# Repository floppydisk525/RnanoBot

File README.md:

# RnanoBot
This github repository contains the KiCAD files and supporting documents for an Arduino Nano shield containing a TB6612 motor driver chip and LSM9DS1TR 9DOF IMU.  

The TB6612 circuit was influenced from https://github.com/floppydisk525/BoxBotCtrlBrd, which in turn was influenced from https://github.com/BoxBots/control-board.  

The LSM9DS1TR chip was influenced from sparkfun projects such as https://www.sparkfun.com/products/13944 and others.  

The repository name RnanoBot comes from "aRduino NANO roBOT" motor shield with TB6612 &amp; LSM9DS1TR.  

### Datasheets  
Datasheets are in the https://github.com/floppydisk525/RnanoBot/tree/master/board/datasheets folder.  
# Typical Application Notes  
Here are typical application images for key componets.  
## TB6612  
![alt text][tb6612]  
## LSM9DS1TR  
![alt text][lsm9ds1]  
The following cut/paste is from:  https://learn.sparkfun.com/tutorials/lsm9ds1-breakout-hookup-guide:  
![alt text][lsm9ds1_spark]  

## Arduino NANO Pinout  
I really like this Arduino NANO pinout from Components 101 https://components101.com/microcontrollers/arduino-nano:  
![alt text][ardnano]

![alt text][ard_dim]

### References
https://learn.sparkfun.com/tutorials/lsm9ds1-breakout-hookup-guide  
https://www.sparkfun.com/products/13944  
https://cdn.sparkfun.com/assets/b/0/f/7/4/SparkFun_Motor_Driver-TB6612FNG_v11c.pdf  
https://www.digikey.com/product-detail/en/stmicroelectronics/LSM9DS1TR/497-14946-1-ND/4988079  
https://www.digikey.com/product-detail/en/toshiba-semiconductor-and-storage/TB6612FNGC8EL/TB6612FNGC8ELCT-ND/1730134  
https://components101.com/microcontrollers/arduino-nano  
https://www.youtube.com/watch?v=gGix1oYhTRs  
https://www.st.com/resource/en/datasheet/lsm9ds1.pdf  
http://cheasokchenda.blogspot.com/2018/05/you-can-click-on-link-bellow-to-get-6.html  

[tb6612]:/board/datasheets/tb6612%20typical%20application%20diagram.PNG "TB6612 Typical Application Diagram"
[lsm9ds1]:/board/datasheets/lsm9ds1%20application%20hints.PNG "LSM9DS1TR Application Hint from Datasheet"
[lsm9ds1_spark]:/board/datasheets/sparkfun%20i2c%20wiring%20image.PNG "LSM9DS1TR Spark Fun I2C Wiring example"
[ardnano]:/board/datasheets/Arduino-Nano-Pinout.png "Arduino NANO Pinout from Components 101"
[ard_dim]:/board/datasheets/arduino%20nano%20dim.PNG "Arduino Physical Dimensions"

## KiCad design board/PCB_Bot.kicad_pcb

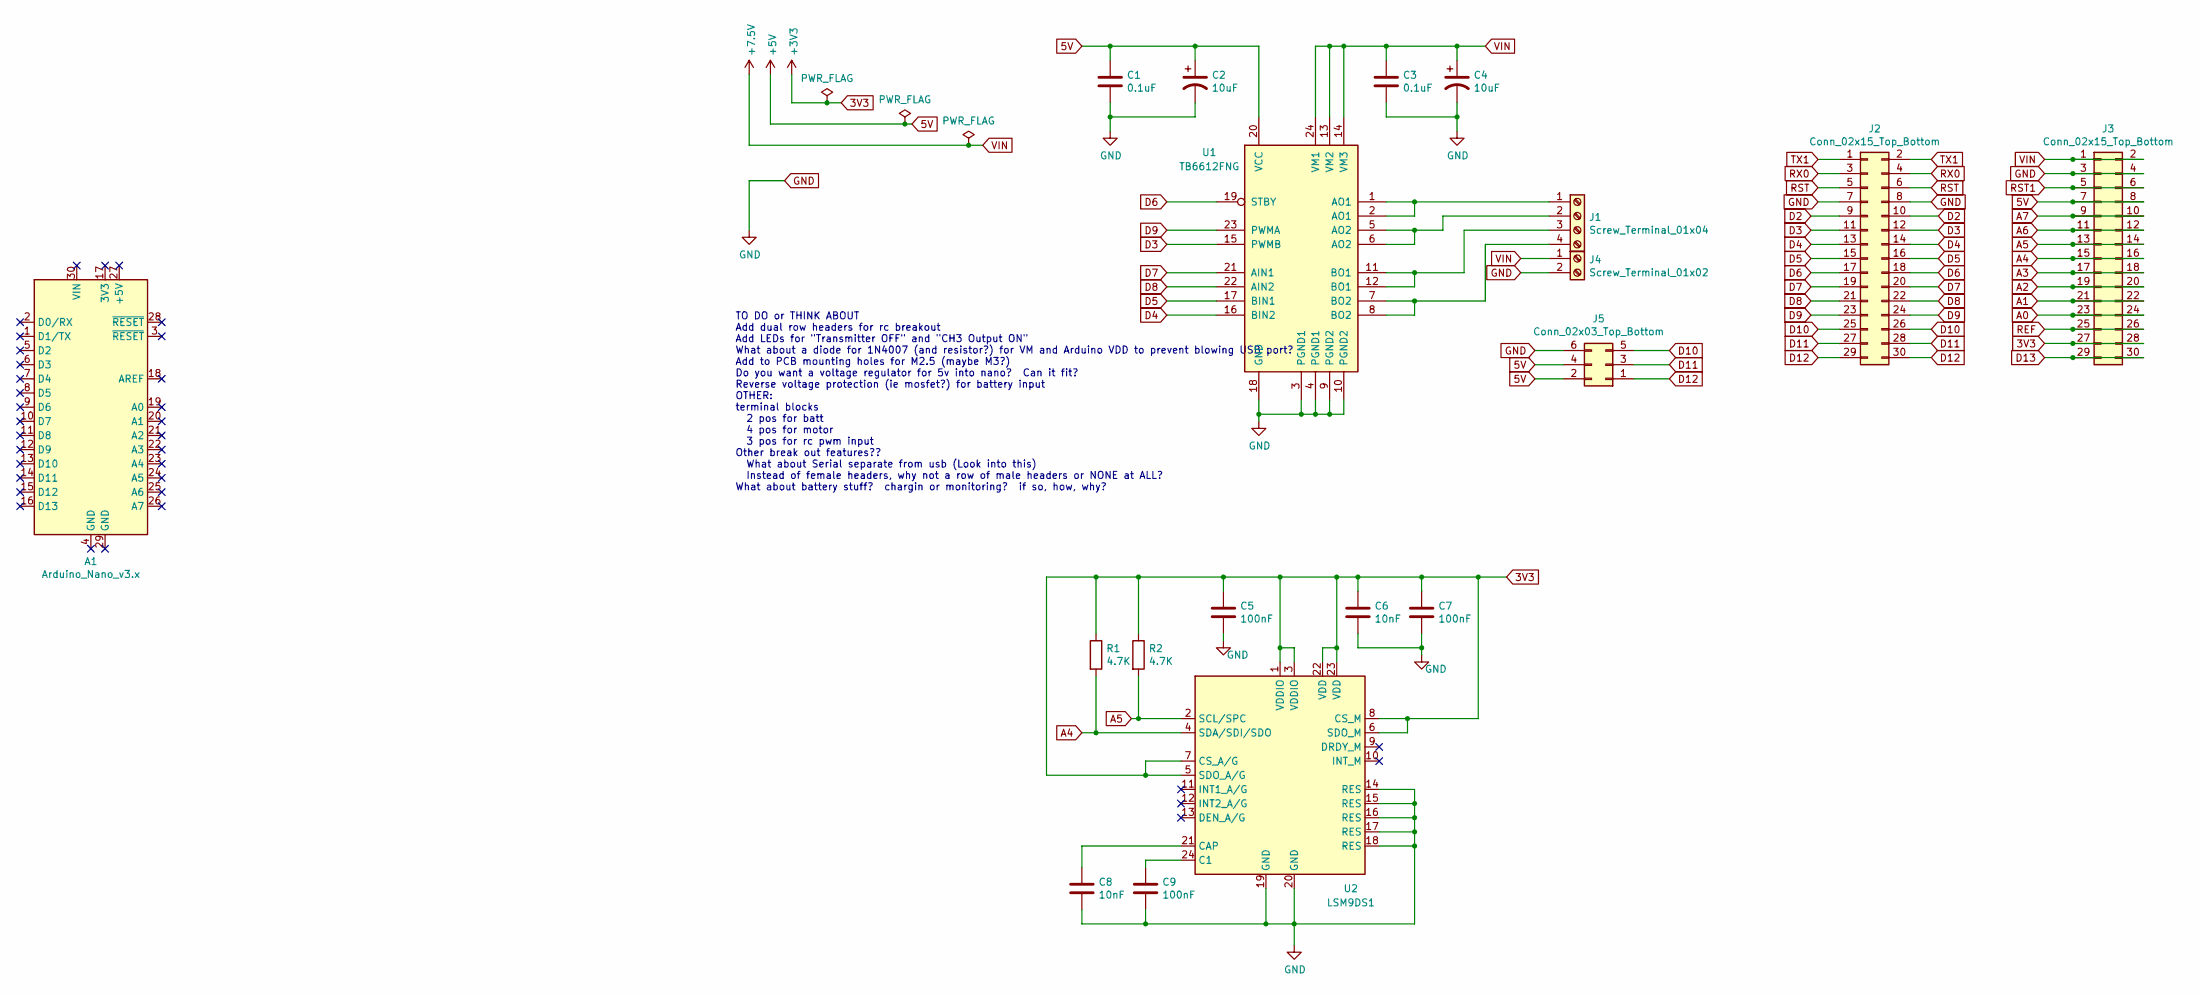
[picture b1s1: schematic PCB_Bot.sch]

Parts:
A1: Arduino_Nano_v3.x; Arduino_Nano
C1, C3: 0.1uF; C_01005_0402Metric
C2, C4: 10uF; C_0201_0603Metric
C5, C7, C9: 100nF; C_01005_0402Metric
C6, C8: 10nF; C_0201_0603Metric
J1: Screw_Terminal_01x04; PTSM_Phoenix_Contact_4-pos_Base_Strip_1815280
J2, J3: Conn_02x15_Top_Bottom; PinSocket_2x15_P2.54mm_Vertical
J4: Screw_Terminal_01x02; PTSM_Phoenix_Contact_2-pos_Base_Strip_1815264
J5: Conn_02x03_Top_Bottom; PinHeader_2x03_P2.54mm_Horizontal
R1, R2: 4.7K; R_01005_0402Metric
U1: TB6612FNG; SSOP-24_5.3x8.2mm_P0.65mm
U2: LSM9DS1; LGA-24L_3x3.5mm_P0.43mm

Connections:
3V3: C5.1, C6.1, C7.1, J3.27, J3.28, R1.1, R2.1, U2.1 (VDDIO), U2.3 (VDDIO), U2.5 (SDO_A/G), U2.6 (SDO_M), U2.7 (CS_A/G), U2.8 (CS_M), U2.22 (VDD), U2.23 (VDD)
5V: C1.1, C2.1, J3.7, J3.8, J5.2, J5.4, U1.20 (VCC)
A0: J3.23, J3.24
A1: J3.21, J3.22
A2: J3.19, J3.20
A3: J3.17, J3.18
A4: J3.15, J3.16, R1.2, U2.4 (SDA/SDI/SDO)
A5: J3.13, J3.14, R2.2, U2.2 (SCL/SPC)
A6: J3.11, J3.12
A7: J3.9, J3.10
D2: J2.9, J2.10
D3: J2.11, J2.12, U1.15 (PWMB)
D4: J2.13, J2.14, U1.16 (BIN2)
D5: J2.15, J2.16, U1.17 (BIN1)
D6: J2.17, J2.18, U1.19 (STBY)
D7: J2.19, J2.20, U1.21 (AIN1)
D8: J2.21, J2.22, U1.22 (AIN2)
D9: J2.23, J2.24, U1.23 (PWMA)
D10: J2.25, J2.26, J5.5
D11: J2.27, J2.28, J5.3
D12: J2.29, J2.30, J5.1
D13: J3.29, J3.30
GND: C1.2, C2.2, C3.2, C4.2, C5.2, C6.2, C7.2, C8.2, C9.2, J2.7, J2.8, J3.3, J3.4, J4.2, J5.6, U1.3 (PGND1), U1.4 (PGND1), U1.9 (PGND2), U1.10 (PGND2), U1.18 (GND), U2.14 (RES), U2.15 (RES), U2.16 (RES), U2.17 (RES), U2.18 (RES), U2.19 (GND), U2.20 (GND)
unnamed: C8.1, U2.21 (CAP)
unnamed: C9.1, U2.24 (C1)
unnamed: J1.1, U1.1 (AO1), U1.2 (AO1)
unnamed: J1.2, U1.5 (AO2), U1.6 (AO2)
unnamed: J1.3, U1.11 (BO1), U1.12 (BO1)
unnamed: J1.4, U1.7 (BO2), U1.8 (BO2)
REF: J3.25, J3.26
RST: J2.5, J2.6
RST1: J3.5, J3.6
RX0: J2.3, J2.4
TX1: J2.1, J2.2
VIN: C3.1, C4.1, J3.1, J3.2, J4.1, U1.13 (VM2), U1.14 (VM3), U1.24 (VM1)

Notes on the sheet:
TO DO or THINK ABOUT Add dual row headers for rc breakout Add LEDs for "Transmitter OFF" and "CH3 Output ON" What about a diode for 1N4007 (and resistor?) for VM and Arduino VDD to prevent blowing USB port? Add to PCB mounting holes for M2.5 (maybe M3?) Do you want a voltage regulator for 5v into n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

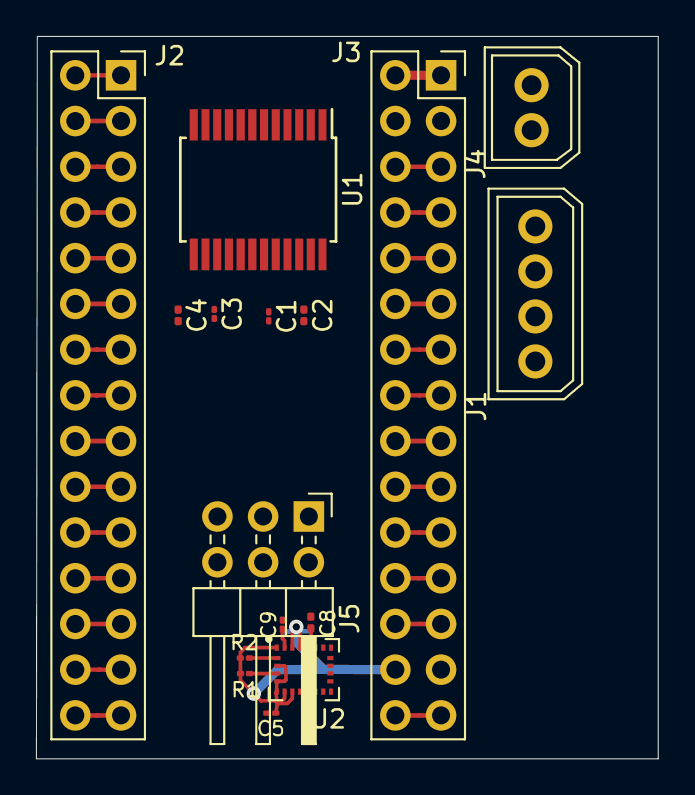
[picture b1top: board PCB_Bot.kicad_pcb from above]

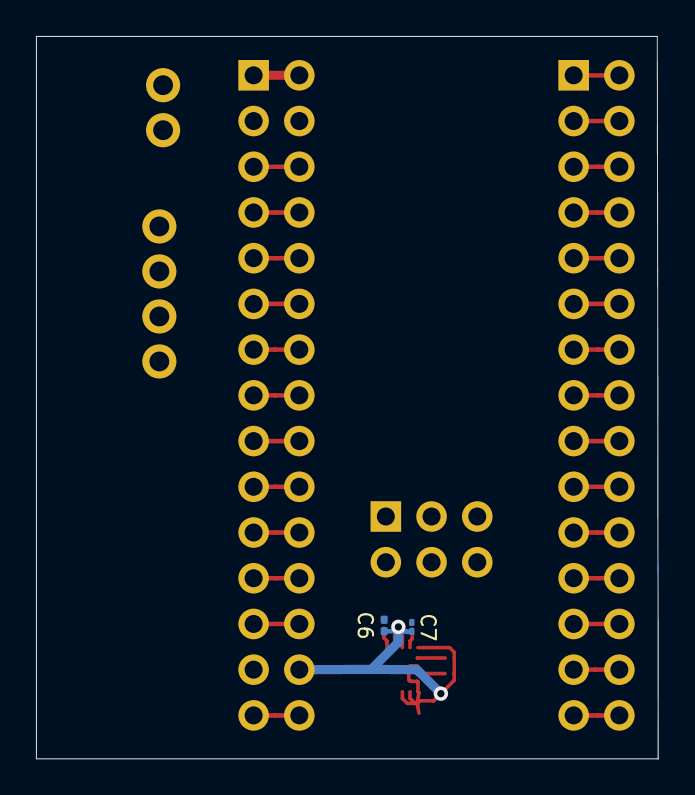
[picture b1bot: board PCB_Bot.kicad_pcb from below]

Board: 2 copper layers, 34.5 x 40.1 mm, 18 parts (2 on the bottom side), 35 nets.

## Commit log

2020-02-22 initial commit of KiCADproject and folder structure setup
2020-02-22 add datasheets, update cgammel notes for github
2020-02-22 update readme.md with references of websites used for design
2020-02-22 add more background to readme.md
2020-02-22 add tb6612 app image to readme.md
2020-02-22 add lsm images to readme.md
2020-02-22 add link to sparkfun image
2020-02-22 add componenets 101 arduino NANA image to readme.md
2020-02-22 update schematic, add 9Dof pdf
2020-02-22 add aduino nano dim.png image
2020-02-22 add dims of arduino nano and link in readme.md
2020-02-22 fix issues w/ readme.md and re format
2020-02-23 add screw terminal to breakout motors and battery input power
2020-02-23 add farad values and update schematic
2020-02-23 spaces at end of line for farad file
2020-02-23 update pcbnew board layout and update foot prints
2020-02-23 boardlayoutexamples.md file uploaded with links and images to fill out file
2020-02-23 update boardlayoutexmaple md
2020-02-23 add box bot images for boardlayoutexmaple.md
2020-02-23 add bold to links in boardlayoutexmaple.md
2020-02-23 more bold to links in boardlayoutexmaple.md
2020-02-23 add ce images to boardlayoutexmxaple.md
2020-02-24 Change connectors in schematic and in pcbnew. add some tracks in pcbnew
2020-02-24 update notes in schematic to better align w/ todo list
2020-02-24 update notes in schematic
2020-02-25 change screw terminals from 1 to 2, add another for RC input
2020-02-25 pcbnew move capacitors and resistors around
2020-02-25 minor schematic changes, upload and turn off.
2020-02-26 update pcbnew orienatation
2020-02-27 update pcbnew, add new track widths
2020-02-29 update farad values.md with digikey links from Gary help
2020-02-29 add table to farad values.md and fix typo
2020-02-29 update table formatting
2020-02-29 change name of faradvalues.md to brd component ref notes.md
2020-02-29 add decoupling cap info to resources and images
2020-03-01 update pcbnew and add some tracks - that can be replaced at some point...
2020-03-01 upload step files for phoenix contact models.
2020-03-01 look at layout of nano, add notes_examples to md files
2020-03-01 typo in board resources md
2020-03-01 fix md file formatting boardcomponentrefntoes.md
2020-03-01 add smt sizes to board...md
2020-03-01 update power flags in schematic, check erros and warnings - all warnings now
2020-03-01 add step files for phoenix contact 2.5mm terminal blocks and update in model.
2020-03-01 add stp files and update boardlayoutex.md
2020-03-01 typo fix in boardlayoutex.md
2020-03-01 add chro connectors to boardrefnotes
2020-03-01 fix text in brdrefnotes.md file
2020-03-02 add terminal block lins (md files) and some datasheets for reference later
2020-03-02 fix typo md file
